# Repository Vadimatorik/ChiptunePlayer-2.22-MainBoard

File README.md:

# ChiptunePlayer-2.22-MainBoard

В прошлой плате обнаружено слишком много недостатков. 

В ветке dev производится разработка новой версии, решающей проблемы текущей версии. 

До момента окончания тестирования она не будет слита в master.

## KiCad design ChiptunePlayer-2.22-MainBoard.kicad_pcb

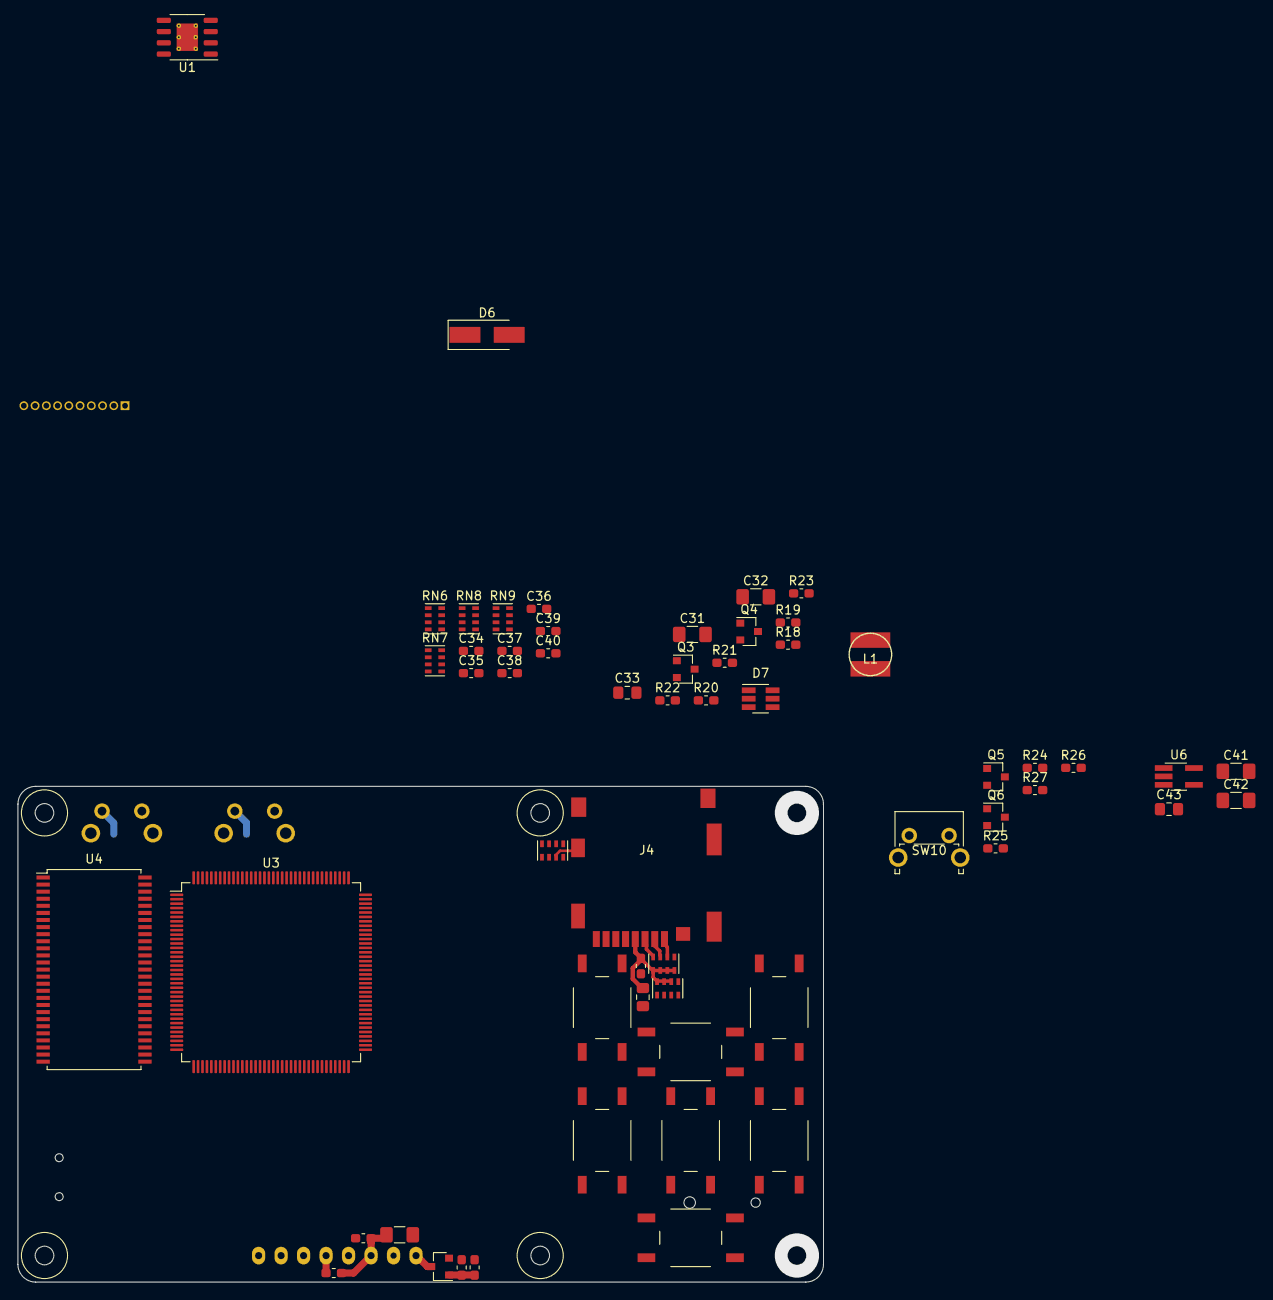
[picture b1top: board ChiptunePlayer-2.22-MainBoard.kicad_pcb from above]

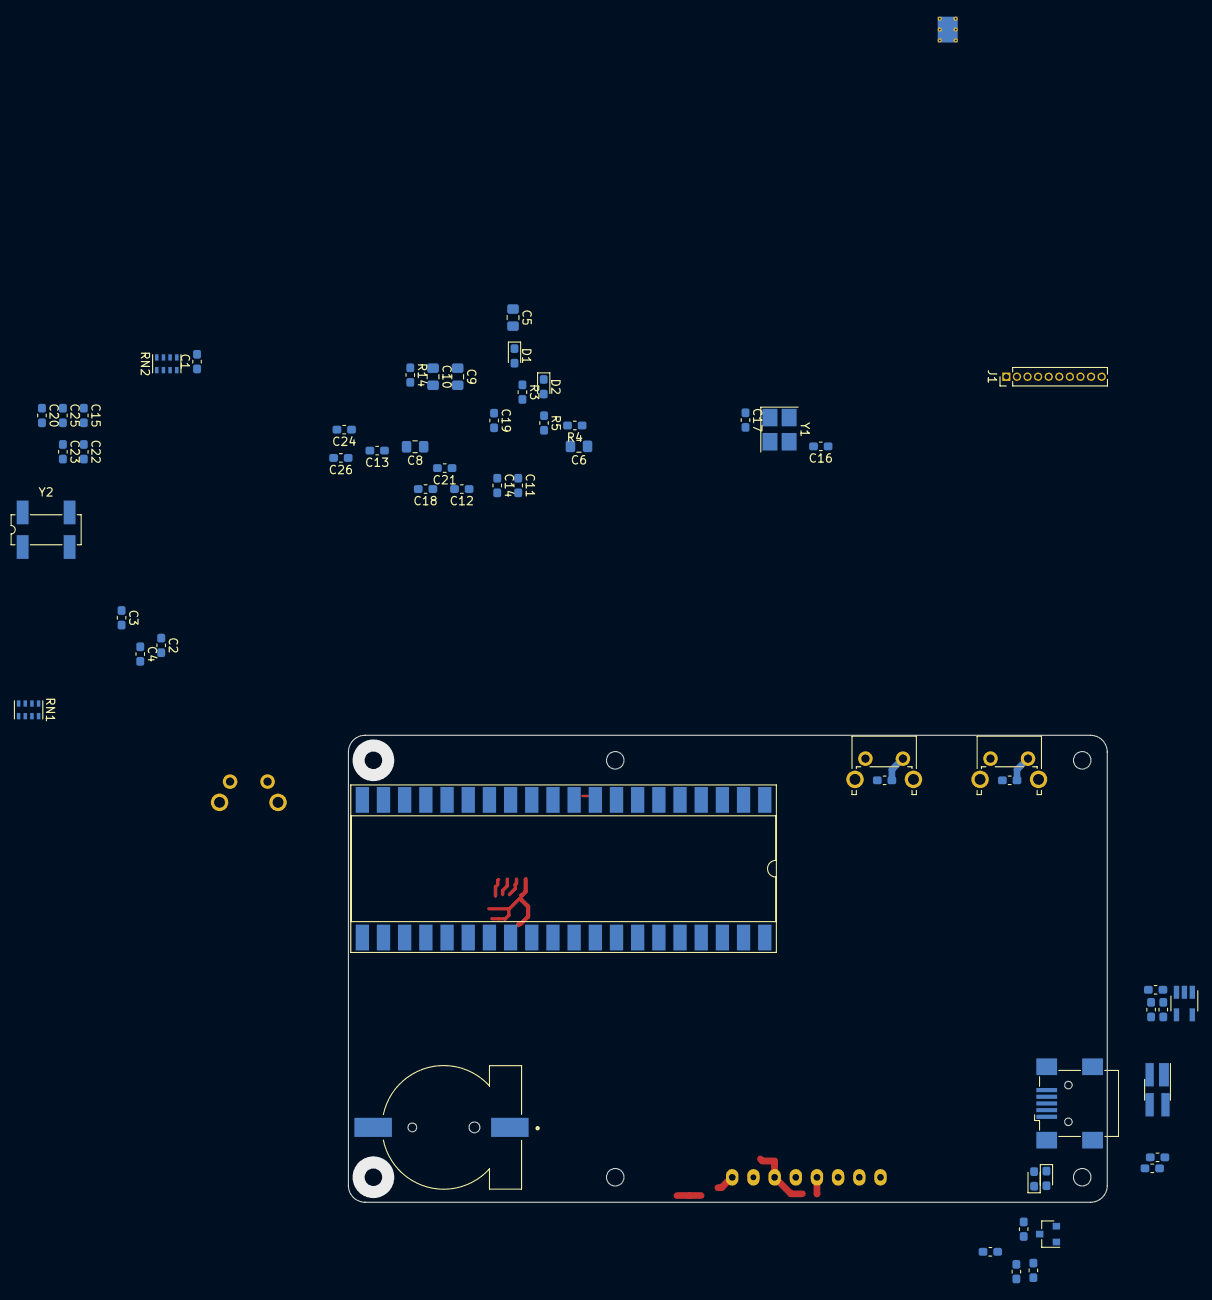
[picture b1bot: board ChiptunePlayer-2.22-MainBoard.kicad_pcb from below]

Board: 2 copper layers, 91.0 x 56.0 mm, 116 parts (57 on the bottom side), 78 nets.

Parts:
BT1: S8411-45R; BAT_S8411-45R
C1, C2, C3, C4, C11, C12, C13, C14, C15, C16, C17, C18, C19, C20, C21, C26, C28, C29, C34, C35, C36, C37, C38, C39, C40: 100nF; C_0603_1608Metric_Pad1.05x0.95mm_HandSolder
C5, C6, C27: 10uF; C_0805_2012Metric_Pad1.15x1.40mm_HandSolder
C7: 4.7uF; C_0603_1608Metric_Pad1.05x0.95mm_HandSolder
C8, C9: 2.2uF; C_0805_2012Metric_Pad1.15x1.40mm_HandSolder
C10: 1uF; C_0805_2012Metric_Pad1.15x1.40mm_HandSolder
C22, C23, C24, C25: 22; C_0603_1608Metric_Pad1.05x0.95mm_HandSolder
C30: 2.2uF; C_1206_3216Metric_Pad1.42x1.75mm_HandSolder
C31: 100uF; C_1206_3216Metric_Pad1.42x1.75mm_HandSolder
C32, C41, C42: 10uF; C_1206_3216Metric_Pad1.42x1.75mm_HandSolder
C33, C43: 100nF; C_0805_2012Metric_Pad1.15x1.40mm_HandSolder
D1: CHRG; LED_0603_1608Metric_Pad1.05x0.95mm_HandSolder
D2: STDBY; LED_0603_1608Metric_Pad1.05x0.95mm_HandSolder
D3: SP0503BAHT; SOT-143_Handsoldering
D4: RED; LED_0603_1608Metric_Pad1.05x0.95mm_HandSolder
D5: GREEN; LED_0603_1608Metric_Pad1.05x0.95mm_HandSolder
D6: 1N4001; D_SMA_Handsoldering
D7: PT1301; SOT-23-6_Handsoldering
J1: Conn_01x10_Male; PinHeader_1x10_P1.27mm_Vertical
J3: USB_OTG; USB_Mini-B_Wuerth_65100516121_Horizontal
J4: 49225-0821
L1: 4.7µH; CD43
LCD1: LCD_COG_12864_ST7565R_SPI; LCD_COG_12864_ST7565R
Q1, Q2, Q3, Q5: BC817; SOT-23
Q4, Q6: IRLML6402; SOT-23
R1, R2, R7, R12, R13, R14, R16, R17, R19, R25: 10K; R_0603_1608Metric_Pad1.05x0.95mm_HandSolder
R3, R4, R8, R9: 330; R_0603_1608Metric_Pad1.05x0.95mm_HandSolder
R5: 1K2; R_0603_1608Metric_Pad1.05x0.95mm_HandSolder
R6, R15, R18, R24: 1K; R_0603_1608Metric_Pad1.05x0.95mm_HandSolder
R10, R11: 22; R_0603_1608Metric_Pad1.05x0.95mm_HandSolder
R20, R26: 4K7; R_0603_1608Metric_Pad1.05x0.95mm_HandSolder
R21, R27: 27; R_0603_1608Metric_Pad1.05x0.95mm_HandSolder
R22: 3M; R_0603_1608Metric_Pad1.05x0.95mm_HandSolder
R23: 1M; R_0603_1608Metric_Pad1.05x0.95mm_HandSolder
RN1, RN2, RN3, RN6, RN7, RN8, RN9: CAT16-103J4; R_Cat16-4
RN4, RN5: CAY16-473J4; R_Cat16-4
SW1: +; SW_Tactile_SPST_Angled_PTS645Vx83-2LFS
SW2: -; SW_Tactile_SPST_Angled_PTS645Vx83-2LFS
SW3: MENY; SW_PUSH_6x6x13
SW4: LEFT; SW_PUSH_6x6x13
SW5: UP; SW_PUSH_6x6x13
SW6: ENTER; SW_PUSH_6x6x13
SW7: DOWN; SW_PUSH_6x6x13
SW8: RETURN; SW_PUSH_6x6x13
SW9: RIGHT; SW_PUSH_6x6x13
SW10: PWR_ON; SW_Tactile_SPST_Angled_PTS645Vx83-2LFS
U1: TP4056; HSOP-8-1EP_3.9x4.9mm_P1.27mm_EP2.41x3.1mm_ThermalVias
U2: STMPS2151STR; SOT-23-5_HandSoldering
U3: STM32F722ZETx; LQFP-144_20x20mm_P0.5mm
U4: W9812G6KH-6; TSOP-II-54_22.2x10.16mm_P0.8mm
U5: YM2149; DIP-40_W16.51mm_SMDSocket_LongPads
U6: NCP551SN33T1G; TSOT-23-5_HandSoldering
Y1: NX3225SA-16.000M-STD-CRS-2; Crystal_SMD_3225-4Pin_3.2x2.5mm_HandSoldering
Y2: MC-306; Crystal_SMD_SeikoEpson_MC306-4Pin_8.0x3.2mm_HandSoldering

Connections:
+3V3: C42.1, C43.1, R8.2, R9.1, R13.1, U6.5
+5V: C32.1, C33.1, D6.1, D7.1, D7.5, R22.1, U2.5
/ADC_CH_A1: C40.1, RN6.8, RN8.1
/ADC_CH_A2: C34.1, RN6.5, RN8.4
/ADC_CH_B1: C38.1, RN6.7, RN8.2
/ADC_CH_B2: C39.1, RN7.7, RN9.2
/ADC_CH_BIPPER: C35.1, RN7.5, RN9.4
/ADC_CH_C1: C36.1, RN6.6, RN8.3
/ADC_CH_C2: C37.1, RN7.6, RN9.3
/ADC_CH_LEFT_IN: C2.1, RN1.6, RN2.3
/ADC_CH_RIGHT: C1.1, RN1.5, RN2.4
/ADC_CH_VDD_BAT: C4.1, RN1.8, RN2.1
/ADC_CH_VDD_USB: C3.1, RN1.7, RN2.2
/BR1: SW3.1, SW5.1, SW8.1
/BR2: SW4.1, SW6.1, SW9.1
/B_MINUS: R2.1, SW2.2
/B_PLUS: R1.1, SW1.2
/CHRG: R3.2, U1.7
/LCD_RES: LCD1.9, R17.1
/OTG_EN: R12.1, U2.4, U3.40
/SC1: RN3.5, SW3.2, SW4.2
/SC2: RN3.6, SW5.2, SW6.2, SW7.2
/SC3: RN3.7, SW8.2, SW9.2
/SD_CMD: J4.3, RN5.8
/SD_CON: J4.10, RN4.7
/SD_D0: J4.7, RN5.5
/SD_D1: J4.8, RN4.8
/SD_D2: J4.1, RN5.6
/SD_D3: J4.2, RN5.7
/STDBY: R4.2, U1.6
/USB_D_+: R10.2, U3.104
/USB_D_-: R11.2, U3.103
/USB_ID: D3.4, J3.4, U3.102
/VBUS_FAULT: D4.1, R13.2, U2.3, U3.42
/adc_inputs_div/VDD_BAT: C41.1, Q6.3, RN1.1, U6.1, U6.3
/adc_inputs_div/VDD_USB: C5.1, C7.1, D1.2, D2.2, J3.1, R6.2, RN1.2, U1.4, U1.8, U2.1
/charging/VDD_BAT: C6.1, Q4.2, Q6.2, R20.1, R26.1, U1.5
/lcd/LCD_PWM: LCD1.5, Q2.3
/mc/CAP_1: C8.2, U3.71
/mc/CAP_2: C9.2, U3.106
/mc/JT_CLK: J1.9, U3.109
/mc/JT_DI: J1.8, U3.110
/mc/JT_DO: J1.7, U3.133
/mc/JT_MS: J1.10, U3.105
/mc/JT_RST: J1.6, U3.134
/mc/NRST: C26.1, J1.3, R14.2, U3.25
/mc/OSC32_IN: C24.2, U3.8, Y2.1
/mc/OSC32_OUT: C25.2, U3.9, Y2.4
/mc/OSC_IN: C22.2, U3.23, Y1.1
/mc/OSC_OUT: C23.2, U3.24, Y1.4
/mc/VDD_R_BAT: BT1.P, C10.2, U3.6
/usb/U_DP_+: D3.3, J3.3, R10.1
/usb/U_DP_-: D3.2, J3.2, R11.1
GND: C1.2, C2.2, C3.2, C4.2, C5.2, C6.2, C7.2, C31.2, C32.2, C33.2, C34.2, C35.2, C36.2, C37.2, C38.2, C39.2, C40.2, C41.2, C42.2, C43.2, D3.1, D7.3, J3.5, J3.6, Q1.2, Q2.2, Q3.2, Q5.2, R5.2, R7.1, R12.2, R16.1, R19.2, R23.2, R25.2, RN2.5, RN2.6, RN2.7, RN2.8, RN8.5, RN8.6, RN8.7, RN8.8, RN9.5, RN9.6, RN9.7, SW10.2, U1.1, U1.3, U1.9, U2.2, U6.2, U6.4
GNDD: BT1.N, C8.1, C9.1, C10.1, C11.1, C12.1, C13.1, C14.1, C15.1, C16.1, C17.1, C18.1, C19.1, C20.1, C21.1, C22.1, C23.1, C24.1, C25.1, C26.2, C27.2, C28.2, C29.2, C30.2, J1.1, J4.6, J4.9, J4.11, LCD1.6, SW1.1, SW2.1, U3.16, U3.38, U3.51, U3.61, U3.83, U3.94, U3.107, U3.120, U3.130, Y1.2, Y1.3, Y2.2, Y2.3
unnamed: C31.1, L1.1, Q4.3
unnamed: D1.1, R3.1
unnamed: D2.1, R4.1
unnamed: D4.2, R9.2
unnamed: D5.1, Q1.3
unnamed: D5.2, R8.1
unnamed: D6.2, D7.4, L1.2
unnamed: D7.6, R22.2, R23.1
unnamed: Q1.1, R6.1, R7.2
unnamed: Q2.1, R15.1, R16.2
unnamed: Q3.1, R18.2, R19.1
unnamed: Q3.3, R21.2
unnamed: Q4.1, R20.2, R21.1
unnamed: Q5.1, R24.2, R25.1
unnamed: Q5.3, R27.2, SW10.1
unnamed: Q6.1, R26.2, R27.1
unnamed: R5.1, U1.2
unnamed: U4.1, U4.14, U4.27
unnamed: U4.3, U4.9, U4.43, U4.49
unnamed: U4.6, U4.12, U4.46, U4.52
unnamed: U4.28, U4.41, U4.54
VDD: C11.2, C12.2, C13.2, C14.2, C15.2, C16.2, C17.2, C18.2, C19.2, C20.2, C21.2, C27.1, C28.1, C29.1, C30.1, J1.2, J4.4, LCD1.7, R1.2, R2.2, R14.1, R17.2, RN3.2, RN3.3, RN3.4, RN4.1, RN4.2, RN5.1, RN5.2, RN5.3, RN5.4, U3.17, U3.30, U3.39, U3.52, U3.62, U3.72, U3.84, U3.95, U3.108, U3.121, U3.131, U3.144
VDDA: U3.32, U3.33

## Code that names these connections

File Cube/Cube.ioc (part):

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Mcu.Name=STM32F415RGTx
Mcu.Package=LQFP64
Mcu.UserName=STM32F415RGTx
PA0-WKUP.GPIOParameters=GPIO_Label
PA0-WKUP.GPIO_Label=ADC_BAT
PA0-WKUP.Signal=ADCx_IN0
PA1.GPIOParameters=GPIO_Label
PA1.GPIO_Label=AMPLIFIER_LEFT
PA1.Signal=ADCx_IN1
PA10.GPIOParameters=GPIO_Label
PA10.GPIO_Label=USB_ID
PA10.Signal=GPIO_Output
PA11.GPIOParameters=GPIO_Label
PA11.GPIO_Label=USB_DM
PA11.Mode=Device_Only
PA11.Signal=USB_OTG_FS_DM
PA12.GPIOParameters=GPIO_Label
PA12.GPIO_Label=USB_DP
PA12.Mode=Device_Only
PA12.Signal=USB_OTG_FS_DP
PA13.GPIOParameters=GPIO_Label
PA13.GPIO_Label=JT_MS
PA13.Mode=JTAG_5_pins
PA13.Signal=SYS_JTMS-SWDIO
PA14.GPIOParameters=GPIO_Label
PA14.GPIO_Label=JT_CLK
PA14.Mode=JTAG_5_pins
PA14.Signal=SYS_JTCK-SWCLK
PA15.GPIOParameters=GPIO_Label
PA15.GPIO_Label=JT_DI
PA15.Mode=JTAG_5_pins
PA15.Signal=SYS_JTDI
PA2.GPIOParameters=GPIO_Label
PA2.GPIO_Label=AMPLIFIER_RIGHT
PA2.Signal=ADCx_IN2
PA3.GPIOParameters=GPIO_Label
PA3.GPIO_Label=PWR_5V_ON
PA3.Signal=GPIO_Output
PA4.GPIOParameters=GPIO_Label
PA4.GPIO_Label=BOARD_GPIO_4
PA4.Signal=GPIO_Output
PA5.GPIOParameters=GPIO_Label
PA5.GPIO_Label=LCD_CLK
PA5.Mode=TX_Only_Simplex_Unidirect_Master
PA5.Signal=SPI1_SCK
PA6.GPIOParameters=GPIO_PuPd,GPIO_Label
PA6.GPIO_Label=BC0
PA6.GPIO_PuPd=GPIO_PULLUP
PA6.Signal=GPIO_Input
PA7.GPIOParameters=GPIO_Label
PA7.GPIO_Label=LCD_TX
PA7.Mode=TX_Only_Simplex_Unidirect_Master
PA7.Signal=SPI1_MOSI
PA8.GPIOParameters=GPIO_Speed,GPIO_Label
PA8.GPIO_Label=LCD_PWM
PA8.GPIO_Speed=GPIO_SPEED_FREQ_VERY_HIGH
PA8.Signal=S_TIM1_CH1
PA9.GPIOParameters=GPIO_Label
PA9.GPIO_Label=USB_VDD
PA9.Mode=Activate_VBUS
PA9.Signal=USB_OTG_FS_VBUS
PB0.GPIOParameters=GPIO_Label
PB0.GPIO_Label=LCD_A0
PB0.Signal=GPIO_Output
PB1.GPIOParameters=GPIO_Label
PB1.GPIO_Label=LCD_CS
PB1.Signal=GPIO_Output
PB10.GPIOParameters=GPIO_Label
PB10.GPIO_Label=BOARD_CLK
PB10.Mode=TX_Only_Simplex_Unidirect_Master
PB10.Signal=SPI2_SCK
PB11.GPIOParameters=GPIO_Label
PB11.GPIO_Label=SD_PUSH
PB11.Signal=GPIO_Input
PB12.GPIOParameters=GPIO_Label
PB12.GPIO_Label=NOT_USED
PB12.Signal=GPIO_Input
PB13.GPIOParameters=GPIO_Label
PB13.GPIO_Label=SD_CD1
PB13.Signal=GPIO_Output
PB14.GPIOParameters=GPIO_Speed,GPIO_PuPd,GPIO_Label
PB14.GPIO_Label=BR2
PB14.GPIO_PuPd=GPIO_NOPULL
PB14.GPIO_Speed=GPIO_SPEED_FREQ_VERY_HIGH
PB14.Signal=GPIO_Output
PB15.GPIOParameters=GPIO_Speed,GPIO_Label
PB15.GPIO_Label=BR1
PB15.GPIO_Speed=GPIO_SPEED_FREQ_VERY_HIGH
PB15.Signal=GPIO_Output
PB2.GPIOParameters=GPIO_Label
PB2.GPIO_Label=LCD_RES
PB2.Signal=GPIO_Output
PB3.GPIOParameters=GPIO_Label
PB3.GPIO_Label=JT_DO
PB3.Mode=JTAG_5_pins
PB3.Signal=SYS_JTDO-SWO
PB4.GPIOParameters=GPIO_Label
PB4.GPIO_Label=JT_RST
PB4.Mode=JTAG_5_pins
PB4.Signal=SYS_JTRST
PB5.GPIOParameters=GPIO_Label
PB5.GPIO_Label=PWR_ON
PB5.Signal=GPIO_Output
PB6.GPIOParameters=GPIO_Label
PB6.GPIO_Label=DEBUG_TX
PB6.Mode=Asynchronous
PB6.Signal=USART1_TX
PB7.GPIOParameters=GPIO_Label
PB7.GPIO_Label=DEBUG_RX
PB7.Mode=Asynchronous
PB7.Signal=USART1_RX
PB8.GPIOParameters=GPIO_Label
PB8.GPIO_Label=BAT_CHRG
PB8.Signal=GPIO_Input
PB9.GPIOParameters=GPIO_Label
PB9.GPIO_Label=DOWN
PB9.Signal=GPIO_Input
PC0.GPIOParameters=GPIO_Label
PC0.GPIO_Label=BOARD_GPIO_1
PC0.Signal=GPIO_Output
PC1.GPIOParameters=GPIO_Label
PC1.GPIO_Label=BOARD_GPIO_2
PC1.Signal=GPIO_Output
PC10.GPIOParameters=GPIO_PuPd,GPIO_Label
PC10.GPIO_Label=SD_D2
PC10.GPIO_PuPd=GPIO_PULLUP
PC10.Mode=SD_4_bits_Wide_bus
PC10.Signal=SDIO_D2
PC11.GPIOParameters=GPIO_PuPd,GPIO_Label
PC11.GPIO_Label=SD_D3
PC11.GPIO_PuPd=GPIO_PULLUP
PC11.Mode=SD_4_bits_Wide_bus
PC11.Signal=SDIO_D3
PC12.GPIOParameters=GPIO_Label
PC12.GPIO_Label=SD_CLK
PC12.Mode=SD_4_bits_Wide_bus
PC12.Signal=SDIO_CK
PC13-ANTI_TAMP.GPIOParameters=GPIO_Label
PC13-ANTI_TAMP.GPIO_Label=BAT_STDBY
PC13-ANTI_TAMP.Signal=GPIO_Input
PC14-OSC32_IN.GPIOParameters=GPIO_Label
PC14-OSC32_IN.GPIO_Label=OSC32_IN
PC14-OSC32_IN.Mode=LSE-External-Oscillator
PC14-OSC32_IN.Signal=RCC_OSC32_IN
PC15-OSC32_OUT.GPIOParameters=GPIO_Label
PC15-OSC32_OUT.GPIO_Label=OSC32_OUT
PC15-OSC32_OUT.Mode=LSE-External-Oscillator
PC15-OSC32_OUT.Signal=RCC_OSC32_OUT
PC2.GPIOParameters=GPIO_Label
PC2.GPIO_Label=BOARD_GPIO_3
PC2.Signal=GPIO_Output
PC3.GPIOParameters=GPIO_Label
PC3.GPIO_Label=BOARD_TX
PC3.Mode=TX_Only_Simplex_Unidirect_Master
PC3.Signal=SPI2_MOSI
PC4.GPIOParameters=GPIO_PuPd,GPIO_Label
PC4.GPIO_Label=BC1
PC4.GPIO_PuPd=GPIO_PULLUP
PC4.Signal=GPIO_Input
PC5.GPIOParameters=GPIO_PuPd,GPIO_Label
PC5.GPIO_Label=BC2
PC5.GPIO_PuPd=GPIO_PULLUP
PC5.Signal=GPIO_Input
PC6.GPIOParameters=GPIO_Speed,GPIO_PuPd,GPIO_Label
PC6.GPIO_Label=BR0
PC6.GPIO_PuPd=GPIO_NOPULL
PC6.GPIO_Speed=GPIO_SPEED_FREQ_VERY_HIGH
PC6.Signal=GPIO_Output
PC7.GPIOParameters=GPIO_Label
PC7.GPIO_Label=UP
PC7.Signal=GPIO_Input
PC8.GPIOParameters=GPIO_PuPd,GPIO_Label
PC8.GPIO_Label=SD_D0
PC8.GPIO_PuPd=GPIO_PULLUP
PC8.Mode=SD_4_bits_Wide_bus
PC8.Signal=SDIO_D0
PC9.GPIOParameters=GPIO_PuPd,GPIO_Label
PC9.GPIO_Label=SD_D1
PC9.GPIO_PuPd=GPIO_PULLUP
PC9.Mode=SD_4_bits_Wide_bus
PC9.Signal=SDIO_D1
PD2.GPIOParameters=GPIO_PuPd,GPIO_Label
PD2.GPIO_Label=SD_CMD
PD2.GPIO_PuPd=GPIO_PULLUP
PD2.Mode=SD_4_bits_Wide_bus
PD2.Signal=SDIO_CMD
PH0-OSC_IN.GPIOParameters=GPIO_Label
PH0-OSC_IN.GPIO_Label=OSC_IN
PH0-OSC_IN.Mode=HSE-External-Oscillator
PH0-OSC_IN.Signal=RCC_OSC_IN
PH1-OSC_OUT.GPIOParameters=GPIO_Label
PH1-OSC_OUT.GPIO_Label=OSC_OUT
PH1-OSC_OUT.Mode=HSE-External-Oscillator
PH1-OSC_OUT.Signal=RCC_OSC_OUT
RCC.HSE_VALUE=16000000
RCC.SYSCLKFreq_VALUE=168000000
RCC.SYSCLKSource=RCC_SYSCLKSOURCE_PLLCLK
board=custom

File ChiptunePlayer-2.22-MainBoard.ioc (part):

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PH0-OSC_IN.Signal=RCC_OSC_IN
PB10.Mode=Simplex_Bidirectional_Master
PG4.Signal=FMC_A14_BA0
PG8.Signal=FMC_SDCLK
PC12.Signal=SDMMC1_CK
PG0.Signal=FMC_A10
PA6.GPIO_Label=VBUS_FAULT
RCC.SYSCLKSource=RCC_SYSCLKSOURCE_HSE
PB6.Signal=USART1_TX
PB6.Mode=Asynchronous
PC3.Signal=FMC_SDCKE0
PD0.Signal=FMC_D2_DA2
PD8.Signal=FMC_D13_DA13
PB3.Mode=JTAG_5_pins
PE9.Signal=FMC_D6_DA6
PC9.Mode=SD_4_bits_Wide_bus
PF3.Signal=FMC_A3
PE10.Signal=FMC_D7_DA7
Mcu.Package=LQFP144
PA10.Signal=USB_OTG_FS_ID
PC11.Mode=SD_4_bits_Wide_bus
PF14.Signal=FMC_A8
PA4.GPIO_Label=OTG_EN
PD15.Signal=FMC_D1_DA1
PA5.Mode=Simplex_Bidirectional_Master
PA6.GPIOParameters=GPIO_Label
PG5.Signal=FMC_A15_BA1
PC2.Signal=FMC_SDNE0
PD1.Signal=FMC_D3_DA3
PC0.Signal=FMC_SDNWE
PC14-OSC32_IN.Signal=RCC_OSC32_IN
PD6.Mode=Asynchronous
PA0-WKUP.Signal=UART4_TX
PD10.Signal=FMC_D15_DA15
PA0-WKUP.Mode=Asynchronous
PA9.Signal=USB_OTG_FS_VBUS
PB10.Signal=SPI2_SCK
PA5.Signal=SPI1_SCK
PC12.Mode=SD_4_bits_Wide_bus
PA1.Mode=Asynchronous
PE14.Signal=FMC_D11_DA11
PE15.Signal=FMC_D12_DA12
PE8.Signal=FMC_D5_DA5
PF13.Signal=FMC_A7
PA13.Mode=JTAG_5_pins
PC8.Mode=SD_4_bits_Wide_bus
PA4.Signal=GPIO_Output
PA11.Signal=USB_OTG_FS_DM
PF4.Signal=FMC_A4
PD2.Signal=SDMMC1_CMD
PC1.Signal=SPI2_MOSI
PC1.Mode=Simplex_Bidirectional_Master
PC3.Mode=SdramChipSelect1_1
Mcu.UserName=STM32F722ZETx
PC10.Signal=SDMMC1_D2
PA11.Mode=OTG/Dual_Role_Device
PG15.Signal=FMC_SDNCAS
PA12.Signal=USB_OTG_FS_DP
PF12.Signal=FMC_A6
PH0-OSC_IN.Mode=HSE-External-Oscillator
PD5.Mode=Asynchronous
RCC.HSE_VALUE=16000000
PA15.Mode=JTAG_5_pins
PB4.Mode=JTAG_5_pins
PE13.Signal=FMC_D10_DA10
PC14-OSC32_IN.Mode=LSE-External-Oscillator
PA14.Mode=JTAG_5_pins
PF11.Signal=FMC_SDNRAS
PB7.Signal=USART1_RX
PH1-OSC_OUT.Mode=HSE-External-Oscillator
PA6.Signal=GPIO_Input
PA15.Signal=SYS_JTDI
PF5.Signal=FMC_A5
PF0.Signal=FMC_A0
PE7.Signal=FMC_D4_DA4
PD6.Signal=USART2_RX
PB4.Signal=SYS_JTRST
PA3.Signal=ADCx_IN3
PC15-OSC32_OUT.Mode=LSE-External-Oscillator
PA7.Mode=Simplex_Bidirectional_Master
PA10.Mode=OTG/Dual_Role_Device
PG1.Signal=FMC_A11
PC11.Signal=SDMMC1_D3
PC8.Signal=SDMMC1_D0
PC10.Mode=SD_4_bits_Wide_bus
PC2.Mode=SdramChipSelect1_1
PD9.Signal=FMC_D14_DA14
PD5.Signal=USART2_TX
PA13.Signal=SYS_JTMS-SWDIO
PA9.Mode=Activate_VBUS
PF2.Signal=FMC_A2
PE11.Signal=FMC_D8_DA8
PC15-OSC32_OUT.Signal=RCC_OSC32_OUT
PA1.Signal=UART4_RX
PD2.Mode=SD_4_bits_Wide_bus
board=custom
PH1-OSC_OUT.Signal=RCC_OSC_OUT
PF15.Signal=FMC_A9
PA4.GPIOParameters=GPIO_Label
PF1.Signal=FMC_A1
Mcu.Name=STM32F722Z(C-E)Tx
PE12.Signal=FMC_D9_DA9
PA2.Signal=ADCx_IN2
PD14.Signal=FMC_D0_DA0
PB3.Signal=SYS_JTDO-SWO
PA12.Mode=OTG/Dual_Role_Device
PB7.Mode=Asynchronous
PA14.Signal=SYS_JTCK-SWCLK
PC9.Signal=SDMMC1_D1
PA7.Signal=SPI1_MOSI

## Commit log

2018-07-20 Перенес из основного репа.
2018-07-20 Удалил Jlink файл и создал пустой проект.
2018-07-20 Добавил необходимые submodule.
2018-07-20 Компилируется.
2018-07-20 Привел чертеж в порядок и вывел SH и SB.
2018-07-20 SH и SB добавлен.
2018-07-20 Добавил gerber файлы.
2018-07-21 Начал подбивать GPIO.
2018-08-17 Программа перенесена в отдельный реп.
2018-08-17 Сгенерировал заново сборочник.
2018-08-17 Сами сборочники.
2019-06-23 Описаны изменения на схеме для обеспечения работоспособности.
2019-11-02 Обновлен файл Cube.
2019-11-02 Поправки о контроллере в TODO.
2019-11-02 Настроил UART в cube.
2019-11-04 Поправил настройки SPI. Для обоих. С учетом работы DMA на LCD.
2019-11-04 Прерывания от SPI.
2019-11-04 Поправил UART и его прерывание.
2019-11-08 Используется TIM6 для прерываний AY.
2019-11-08 Коэффициенты для tim1. PWM.
2019-11-08 Настройки таймера поправил.
2020-01-16 Поправил назначение выводов для пинов клавиатуры.
2020-01-18 Поправил Cube файл.
2020-02-07 Обновление TODO.
2020-02-08 Правка TODO.
2020-04-15 Размещено предупреждение, что прошлая версия была неудачной.
2020-04-15 Удалил файл .gitmodules.
2020-04-15 Удалил мусор.
2020-04-17 Добавлен .gitignore для kicad.
2020-04-17 Добавил пустышку платы.
2020-04-17 Начал рисовать часть USB.
2020-04-18 Добавлена часть зарядки, клавиши +-, поправлен USB, все разделено на вложенные листи.
2020-04-19 Запитал МК, добавил цепи питания, тактирования, модуль клавиатуры.
2020-04-22 Добавил LCD. Уже есть набросок формата платы с экраном и кнопками.
2020-04-26 dcdc доделан на 5V.
2020-04-27 Сделал плату компактнее.
2020-04-28 Расставил проверенные блоки в столбец.
2020-05-01 Фикс перехода.
2020-05-01 Master пока не говтов.
2020-05-01 Доделал цепь питания.
